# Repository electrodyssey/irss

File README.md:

Infrared soldering station controller with a two Pt100 temperature sensors and 8 pwm outputs

Warning: this is only a working prototype and hasn't been completely tested yet (temperature readout is already working, other things are in progress).

Warning: Please disregard the i2c labels on the MCP3551 interface, it's SPI really =) I've naming it i2c by mistake.

Firmware will be available later in a different repository

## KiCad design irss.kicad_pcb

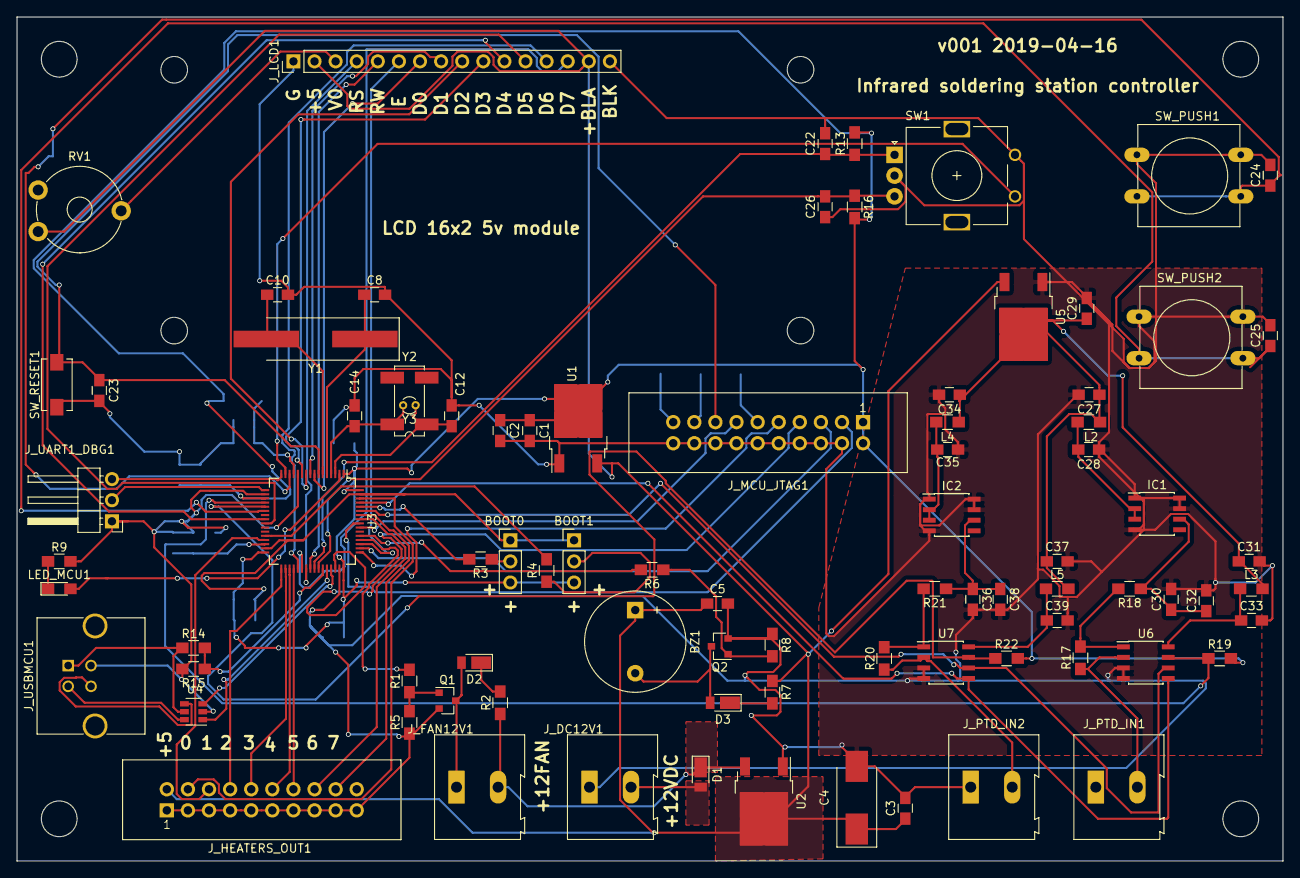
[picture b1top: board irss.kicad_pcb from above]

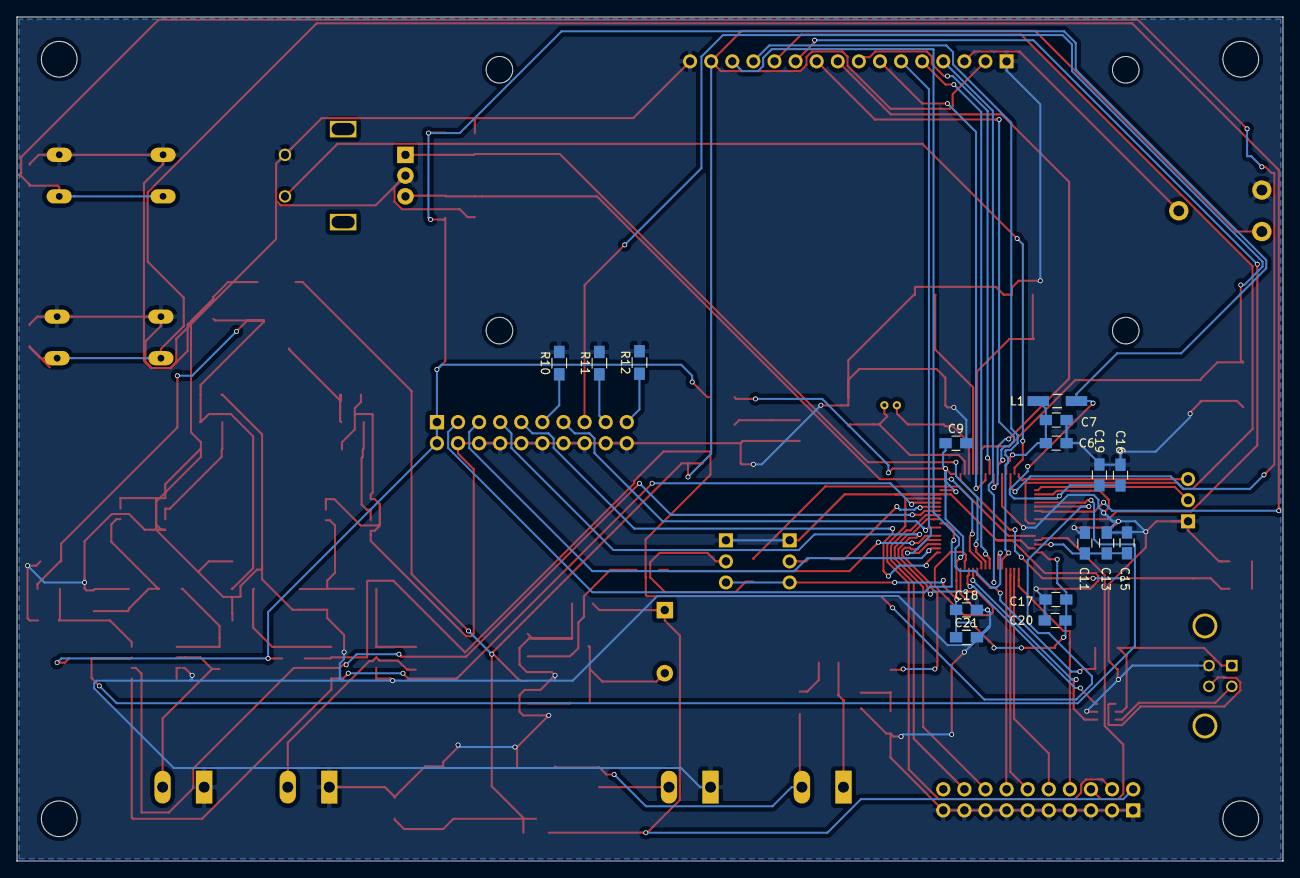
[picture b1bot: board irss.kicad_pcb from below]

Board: 2 copper layers, 152.4 x 101.6 mm, 109 parts (16 on the bottom side), 82 nets.

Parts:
BOOT0, BOOT1: Jumper_NC_Dual; Pin_Header_Straight_1x03_Pitch2.54mm
BZ1: Buzzer; Buzzer_12x9.5RM7.6
C1, C29: 10uF; C_0805_HandSoldering
C2, C3, C7, C9, C15, C19, C20, C21, C22, C23, C24, C25, C26, C28, C32, C33, C35, C38, C39: 0.1; C_0805_HandSoldering
C4: 49; CP_Tantalum_Case-D_EIA-7343-31_Hand
C5, C6, C16, C17, C18, C27, C30, C31, C34, C36, C37: 1uF; C_0805_HandSoldering
C8, C10: 20pF; C_0805_HandSoldering
C11, C13: 2.2uF; C_0805_HandSoldering
C12, C14: 4.3pF; C_0805_HandSoldering
D1, D2, D3: DFLS1100-7; D_PowerDI-123
IC1, IC2: LM4140ACM-2.0; SOIC-8_3.9x4.9mm_Pitch1.27mm
J_DC12V1: Conn_01x02; TerminalBlock_Altech_AK300-2_P5.00mm
J_FAN12V1: Conn_01x02; TerminalBlock_Altech_AK300-2_P5.00mm
J_HEATERS_OUT1: Conn_02x10_Odd_Even; IDC_Header_Straight_20pins
J_LCD1: Conn_01x16; Pin_Header_Straight_1x16_Pitch2.54mm
J_MCU_JTAG1: Conn_02x10_Odd_Even; IDC_Header_Straight_20pins
J_PTD_IN1, J_PTD_IN2: Conn_01x02; TerminalBlock_Altech_AK300-2_P5.00mm
J_UART1_DBG1: Conn_01x03; Pin_Header_Angled_1x03_Pitch2.54mm
J_USBMCU1: USB_B; USB_B_MUSB_Straight
L1: Ferrite_Bead; Choke_SMD_1206_Handsoldering
L2, L3, L4, L5: Ferrite_Bead; R_0805_HandSoldering
LCDMH0, LCDMH1, LCDMH02, LCDMH3: MountingHole_3.2mm_M3
LED_MCU1: LED; LED_0805_HandSoldering
MH0, MH1, MH2, MH3: MountingHole_4.3mm_M4
Q1, Q2: IRLML6344TRPbF; SOT-23
R1, R6: 130; R_0805_HandSoldering
R2, R7: 1k; R_0805_HandSoldering
R3, R4, R5, R8, R10, R11, R12, R13, R16: 10k; R_0805_HandSoldering
R9: 120; R_0805_HandSoldering
R14: 47k; R_0805_HandSoldering
R15: 68k; R_0805_HandSoldering
R17, R18, R20, R21: 6k8; R_0805_HandSoldering
R19, R22: DNP; R_0805_HandSoldering
RV1: 10k DNP; Potentiometer_Trimmer_Piher_PT-10v10_Horizontal_Px10.0mm_Py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
SW1: Rotary_Encoder_DNP; RotaryEncoder_Alps_EC11E_Vertical_H20mm
SW_PUSH1, SW_PUSH2: SW_Push; SW_PUSH-12mm
SW_RESET1: SW_Push; SW_SPST_EVQPE1
U1, U5: AZ1117-3.3; TO-252-2
U2: AZ1117-5.0; TO-252-2
U3: STM32F401RETx; LQFP-64_10x10mm_Pitch0.5mm
U4: USBLC6-2SC6; SOT-23-6
U6, U7: MCP3551-E/MS; SOIC-8_3.9x4.9mm_Pitch1.27mm
Y1: 8MHz; Crystal_SMD_HC49-SD_HandSoldering
Y2: ABS25-32.768KHZ-6-T; Crystal_SMD_SeikoEpson_MC306-4pin_8.0x3.2mm_HandSoldering
Y3: DNP32; Crystal_DS10_d1.0mm_l4.3mm_Vertical

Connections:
+3.3VADC: C27.1, C29.1, C31.1, C34.1, C37.1, L2.2, L3.2, L4.2, L5.2, U5.2
+3V3: BOOT0.3, BOOT1.3, C1.1, C2.1, C9.1, C16.1, C17.1, C18.1, C19.1, C20.1, C21.1, J_MCU_JTAG1.1, J_MCU_JTAG1.2, L1.2, R13.2, R16.2, R19.2, R22.2, U1.2, U3.1, U3.19, U3.32, U3.48, U3.64
+5V: BZ1.1, C3.1, C4.1, C5.1, J_HEATERS_OUT1.2, J_LCD1.2, J_LCD1.15, R7.1, RV1.1, U1.3, U2.2, U5.3
+12V: D1.1, J_FAN12V1.2, R2.1, U2.3
/MCU/BOOT_0: R3.2, U3.60
/MCU/BOOT_1: R4.2, U3.28
/MCU/ENC_CH1: C22.2, R13.1, SW1.1, U3.41
/MCU/ENC_CH2: C26.2, R16.1, SW1.3, U3.42
/MCU/ENC_PUSH_BTN: SW1.4, U3.15
/MCU/I2C_CS0: R19.1, U3.20, U6.7
/MCU/I2C_CS1: R22.1, U3.21, U7.7
/MCU/I2C_SCL: U3.61, U6.5, U7.5
/MCU/I2C_SDA: U3.59, U6.6, U7.6
/MCU/LCD_D0: J_LCD1.7, U3.8
/MCU/LCD_D1: J_LCD1.8, U3.9
/MCU/LCD_D2: J_LCD1.9, U3.10
/MCU/LCD_D3: J_LCD1.10, U3.11
/MCU/LCD_D4: J_LCD1.11, U3.24
/MCU/LCD_D5: J_LCD1.12, U3.25
/MCU/LCD_D6: J_LCD1.13, U3.37
/MCU/LCD_D7: J_LCD1.14, U3.38
/MCU/LCD_E: J_LCD1.6, U3.51
/MCU/LCD_RS: J_LCD1.4, U3.39
/MCU/LCD_RW: J_LCD1.5, U3.40
/MCU/NRST: C23.1, J_MCU_JTAG1.15, SW_RESET1.2, U3.7
/MCU/OUT0: J_HEATERS_OUT1.4, U3.62
/MCU/OUT1: J_HEATERS_OUT1.6, U3.29
/MCU/OUT2: J_HEATERS_OUT1.8, U3.33
/MCU/OUT3: J_HEATERS_OUT1.10, U3.34
/MCU/OUT4: J_HEATERS_OUT1.12, U3.35
/MCU/OUT5: J_HEATERS_OUT1.14, U3.36
/MCU/OUT6: J_HEATERS_OUT1.16, U3.57
/MCU/OUT7: J_HEATERS_OUT1.18, U3.58
/MCU/OUT_BUZZR: R6.2, U3.53
/MCU/OUT_FAN: R1.2, U3.52
/MCU/PUSH_BTN1: C24.1, SW_PUSH1.2, U3.14
/MCU/PUSH_BTN2: C25.1, SW_PUSH2.2, U3.22
/MCU/TCK_SWCLK: J_MCU_JTAG1.9, U3.49
/MCU/TDI: J_MCU_JTAG1.5, U3.50
/MCU/TDO_SWO: J_MCU_JTAG1.13, U3.55
/MCU/TMS_SWDIO: J_MCU_JTAG1.7, U3.46
/MCU/TRST: J_MCU_JTAG1.3, U3.56
/MCU/USART2_RX: J_UART1_DBG1.2, U3.17
/MCU/USART2_TX: J_UART1_DBG1.3, U3.16
/MCU/USB_DETECT: R14.2, R15.1, U3.43
/MCU/USB_DM: U3.44, U4.1
/MCU/USB_DP: U3.45, U4.3
GND: BOOT0.1, BOOT1.1, C1.2, C2.2, C3.2, C4.2, C5.2, C6.2, C7.2, C8.2, C9.2, C10.2, C11.2, C12.2, C13.2, C14.2, C15.2, C16.2, C17.2, C18.2, C19.2, C20.2, C21.2, C22.1, C23.2, C24.2, C25.2, C26.1, C27.2, C28.2, C29.2, C30.2, C31.2, C32.2, C33.2, C34.2, C35.2, C36.2, C37.2, C38.2, C39.2, IC1.1, IC1.4, IC1.7, IC1.8, IC2.1, IC2.4, IC2.7, IC2.8, J_DC12V1.1, J_HEATERS_OUT1.1, J_HEATERS_OUT1.3, J_HEATERS_OUT1.5, J_HEATERS_OUT1.7, J_HEATERS_OUT1.9, J_HEATERS_OUT1.11, J_HEATERS_OUT1.13, J_HEATERS_OUT1.15, J_HEATERS_OUT1.17, J_HEATERS_OUT1.19, J_LCD1.1, J_LCD1.16, J_MCU_JTAG1.4, J_MCU_JTAG1.6, J_MCU_JTAG1.8, J_MCU_JTAG1.10, J_MCU_JTAG1.12, J_MCU_JTAG1.14, J_MCU_JTAG1.16, J_MCU_JTAG1.18, J_MCU_JTAG1.20, J_PTD_IN1.1, J_PTD_IN2.1, J_UART1_DBG1.1, J_USBMCU1.4, Q1.2, Q2.2, R5.1, R8.1, R9.2, R10.2, R11.2, R12.2, R15.2, RV1.3, SW1.2, SW1.5, SW_PUSH1.1, SW_PUSH2.1, SW_RESET1.1, U1.1, U2.1, U3.12, U3.18, U3.31, U3.47, U3.63, U4.2, U5.1, U6.3, U6.4, U7.3, U7.4
unnamed: BZ1.2, D3.2, Q2.3
unnamed: C6.1, C7.1, L1.1, U3.13
unnamed: C8.1, U3.5, Y1.1
unnamed: C10.1, U3.6, Y1.2
unnamed: C11.1, C13.1, C15.1, U3.30
unnamed: C12.1, U3.3, Y2.1, Y3.1
unnamed: C14.1, U3.4, Y2.4, Y3.2
unnamed: C28.1, IC1.2, IC1.3, L2.1
unnamed: C30.1, C32.1, IC1.6, R18.1
unnamed: C33.1, L3.1, U6.8
unnamed: C35.1, IC2.2, IC2.3, L4.1
unnamed: C36.1, C38.1, IC2.6, R21.1
unnamed: C39.1, L5.1, U7.8
unnamed: D1.2, J_DC12V1.2
unnamed: D2.1, R2.2
unnamed: D2.2, J_FAN12V1.1, Q1.3
unnamed: D3.1, R7.2
unnamed: BOOT0.2, R3.1
unnamed: BOOT1.2, R4.1
unnamed: J_LCD1.3, RV1.2
unnamed: J_MCU_JTAG1.11, R10.1
unnamed: J_MCU_JTAG1.17, R11.1
unnamed: J_MCU_JTAG1.19, R12.1
unnamed: J_PTD_IN1.2, R17.1, U6.2
unnamed: J_PTD_IN2.2, R20.1, U7.2
unnamed: J_USBMCU1.1, R14.1, U4.5
unnamed: J_USBMCU1.2, U4.6
unnamed: J_USBMCU1.3, U4.4
unnamed: LED_MCU1.1, R9.1
unnamed: LED_MCU1.2, U3.2
unnamed: Q1.1, R1.1, R5.2
unnamed: Q2.1, R6.1, R8.2
unnamed: R17.2, R18.2, U6.1
unnamed: R20.2, R21.2, U7.1

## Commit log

2019-04-17 irss Initial import
2019-05-15 irss README.md is updated with an "i2c waringing"
